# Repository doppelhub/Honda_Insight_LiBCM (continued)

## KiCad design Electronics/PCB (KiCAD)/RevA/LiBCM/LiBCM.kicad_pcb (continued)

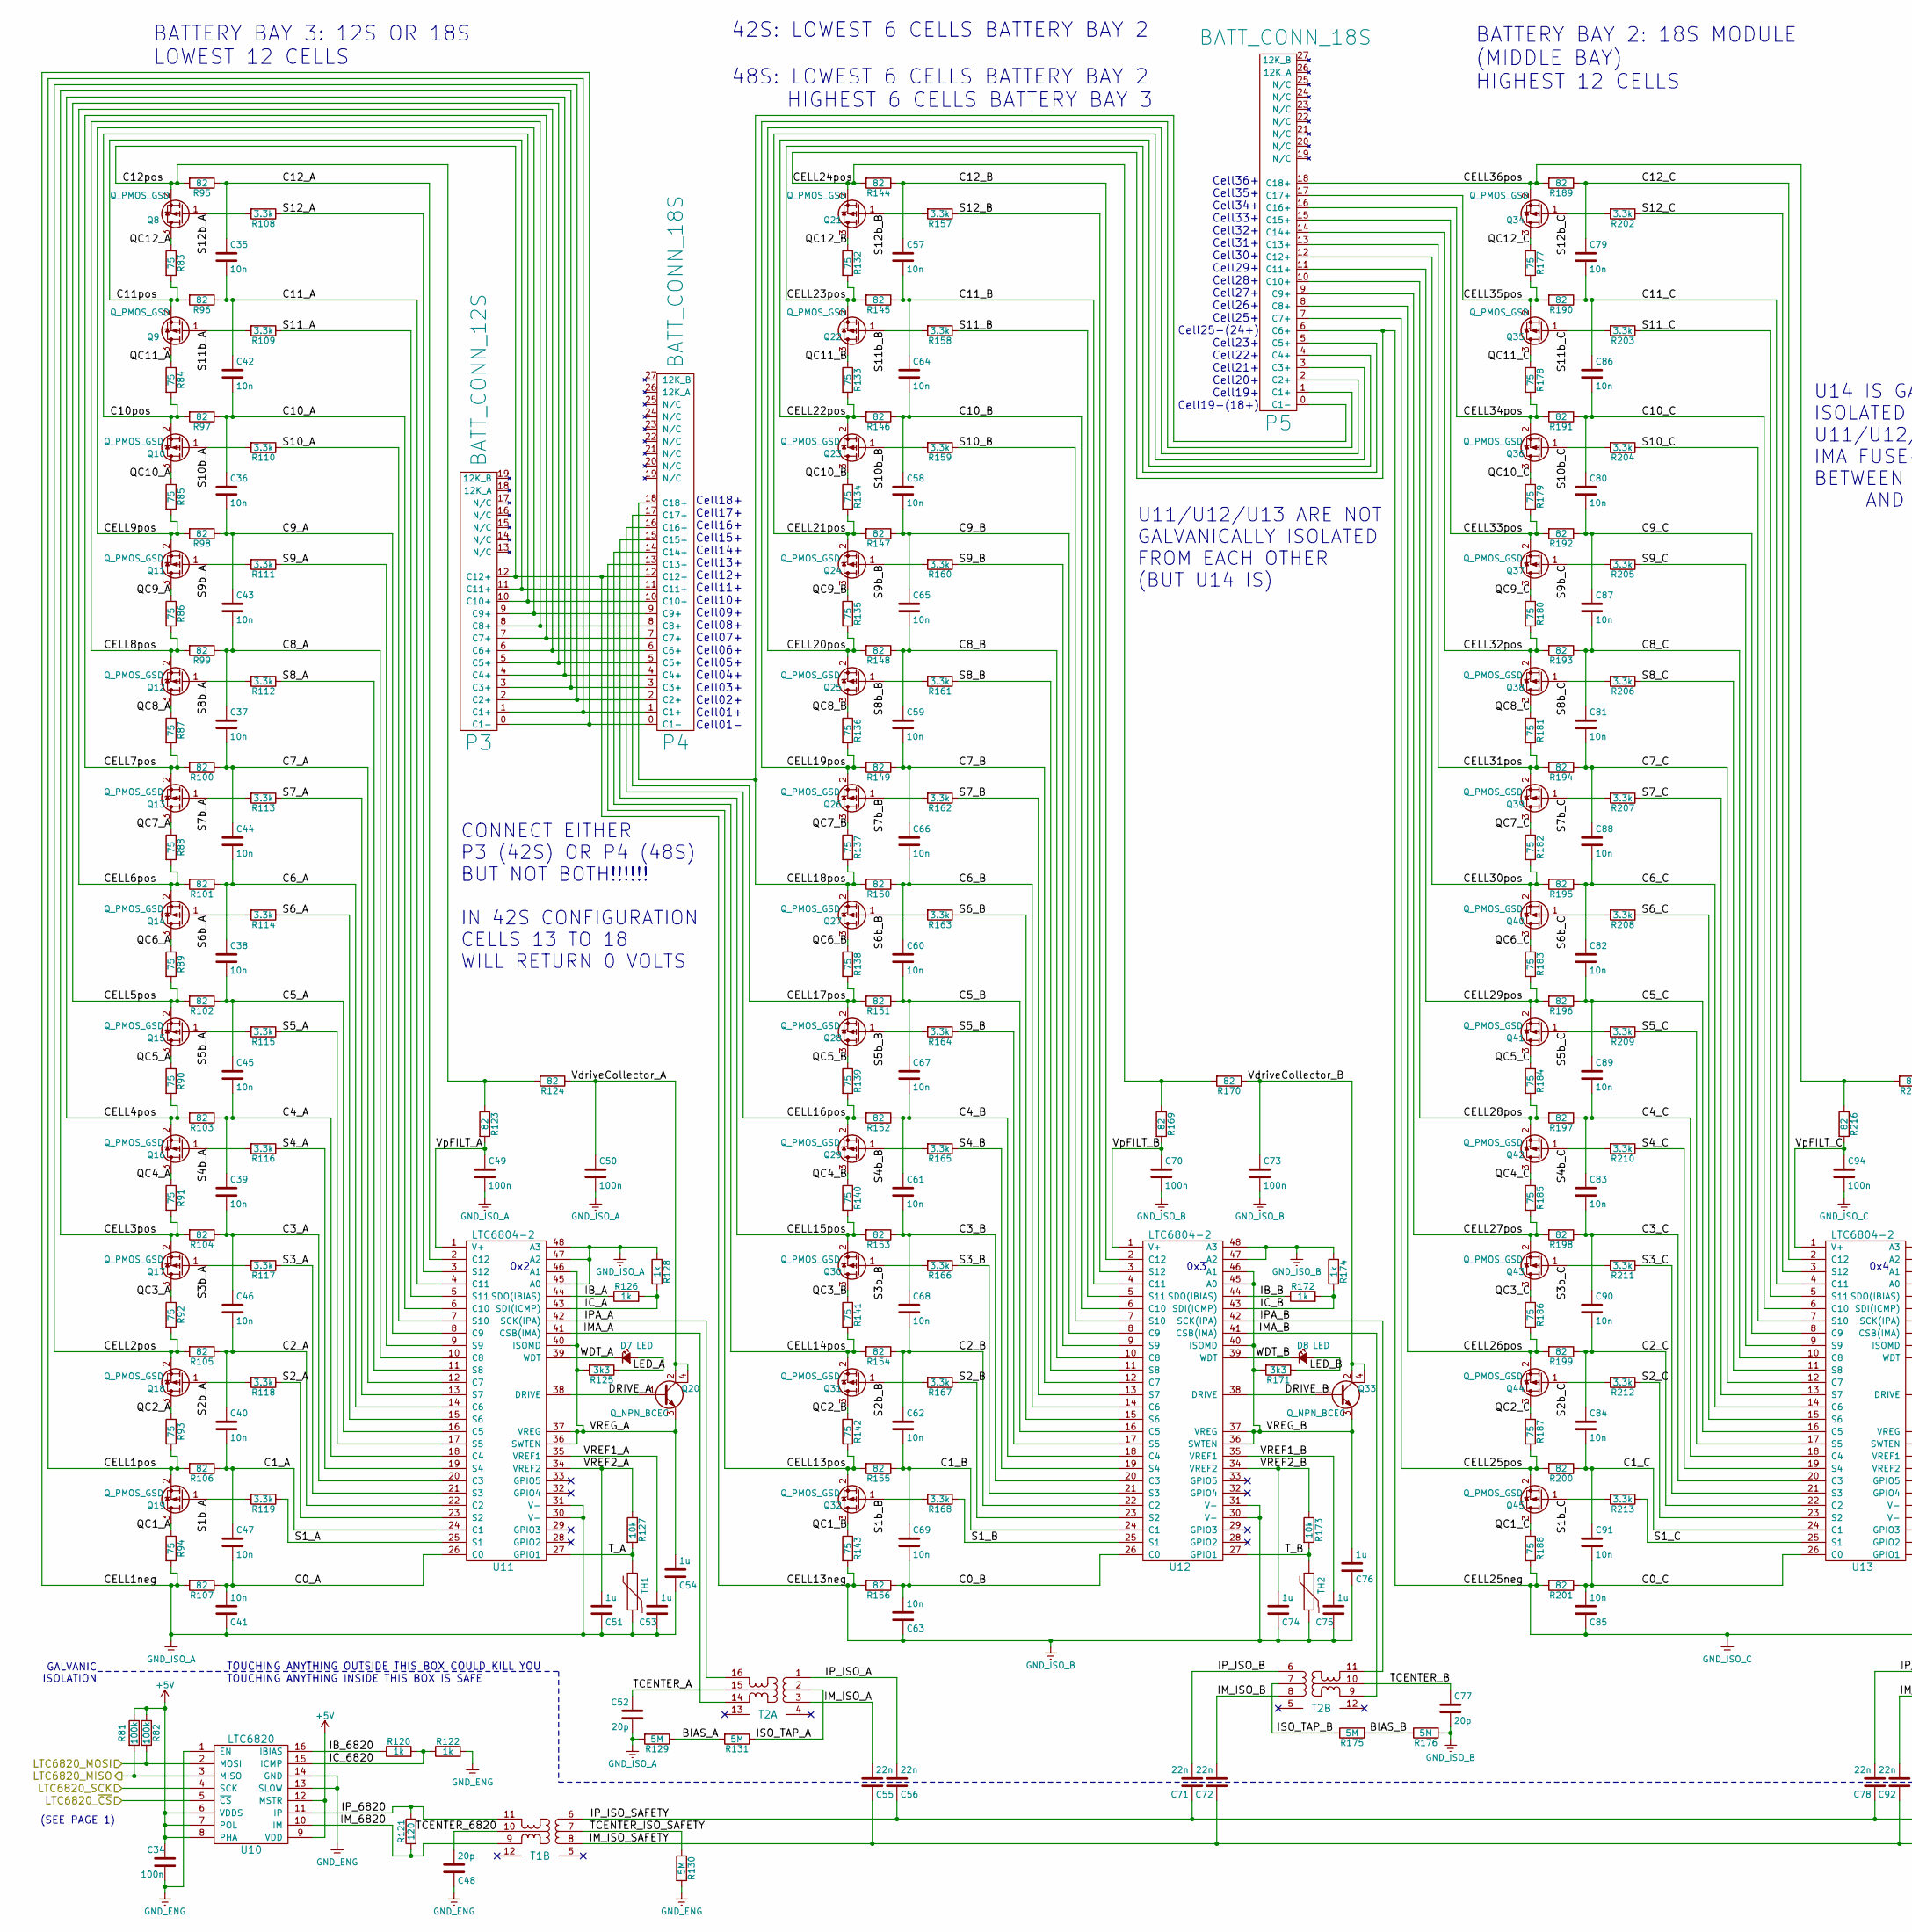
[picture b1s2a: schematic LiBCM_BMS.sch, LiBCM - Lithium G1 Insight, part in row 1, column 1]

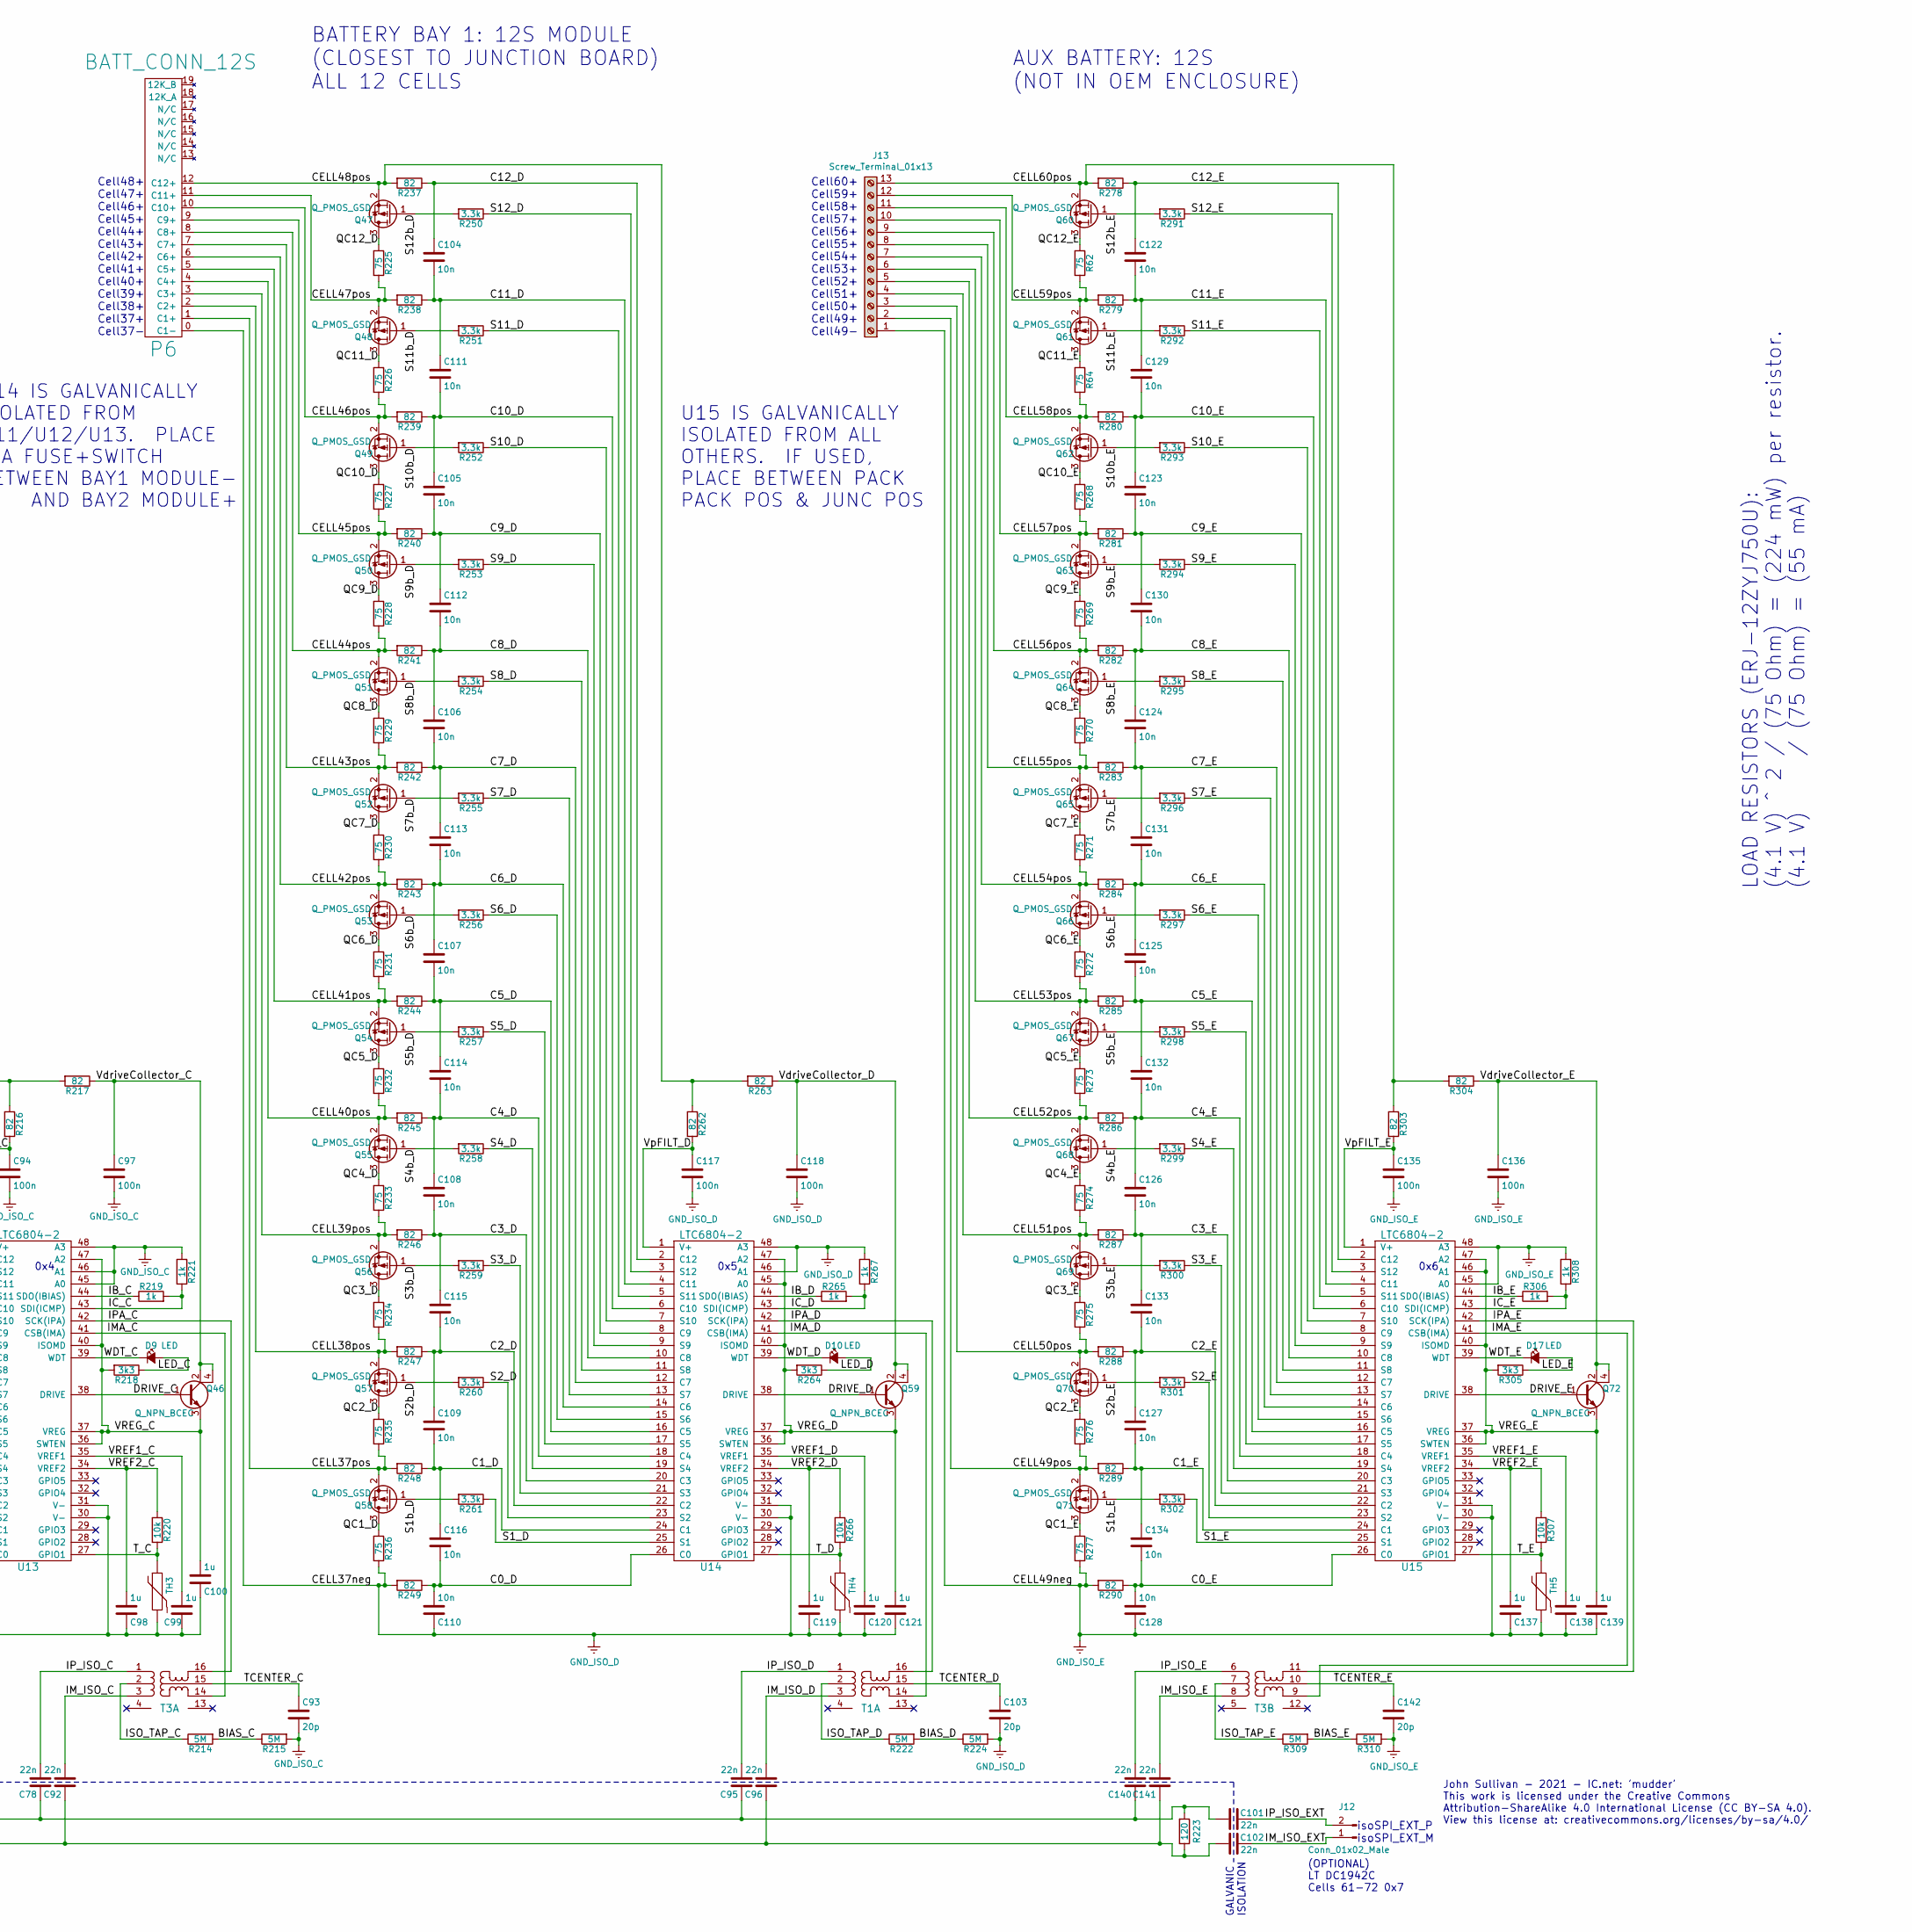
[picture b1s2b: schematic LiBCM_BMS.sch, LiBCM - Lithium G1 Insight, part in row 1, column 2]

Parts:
C34, C49, C50, C70, C73, C94, C97, C117, C118, C135, C136: 100n; C_0805_2012Metric
C35, C36, C37, C38, C39, C40, C41, C42, C43, C44, C45, C46, C47, C57, C58, C59, C60, C61, C62, C63, C64, C65, C66, C67, C68, C69, C79, C80, C81, C82, C83, C84, C85, C86, C87, C88, C89, C90, C91, C104, C105, C106, C107, C108, C109, C110, C111, C112, C113, C114, C115, C116, C122, C123, C124, C125, C126, C127, C128, C129, C130, C131, C132, C133, C134: 10n; C_0805_2012Metric
C48, C52, C77, C93, C103, C142: 20p; C_0805_2012Metric
C51, C53, C54, C74, C75, C76, C98, C99, C100, C119, C120, C121, C137, C138, C139: 1u; C_0805_2012Metric
C55, C56, C71, C72, C78, C92, C95, C96, C101, C102, C140, C141: 22n; C_1206_3216Metric
D7, D8, D9, D10, D17: LED; LED_0805_2012Metric_Castellated
J12: Conn_01x02_Male; SolderWire-0.25sqmm_1x02_P4.2mm_D0.65mm_OD1.7mm
J13: Screw_Terminal_01x13; Conn_277-1232-ND
P3, P6: BATT_CONN_12S; CONN_HONDA-12S
P4, P5: BATT_CONN_18S; CONN_HONDA-18S
Q8, Q9, Q10, Q11, Q12, Q13, Q14, Q15, Q16, Q17, Q18, Q19, Q21, Q22, Q23, Q24, Q25, Q26, Q27, Q28, Q29, Q30, Q31, Q32, Q34, Q35, Q36, Q37, Q38, Q39, Q40, Q41, Q42, Q43, Q44, Q45, Q47, Q48, Q49, Q50, Q51, Q52, Q53, Q54, Q55, Q56, Q57, Q58, Q60, Q61, Q62, Q63, Q64, Q65, Q66, Q67, Q68, Q69, Q70, Q71: Q_PMOS_GSD; SOT-23; Digikey BSS308PE-H6327TR-ND
Q20, Q33, Q46, Q59, Q72: Q_NPN_BCEC; SOT-223; Digikey BCP56-16T1GOSTR-ND
R62, R64, R83, R84, R85, R86, R87, R88, R89, R90, R91, R92, R93, R94, R132, R133, R134, R135, R136, R137, R138, R139, R140, R141, R142, R143, R177, R178, R179, R180, R181, R182, R183, R184, R185, R186, R187, R188, R225, R226, R227, R228, R229, R230, R231, R232, R233, R234, R235, R236, R268, R269, R270, R271, R272, R273, R274, R275, R276, R277: 75; R_2010_5025Metric
R81, R82: 100k; R_0805_2012Metric
R95, R96, R97, R98, R99, R100, R101, R102, R103, R104, R105, R106, R107, R123, R124, R144, R145, R146, R147, R148, R149, R150, R151, R152, R153, R154, R155, R156, R169, R170, R189, R190, R191, R192, R193, R194, R195, R196, R197, R198, R199, R200, R201, R216, R217, R237, R238, R239, R240, R241, R242, R243, R244, R245, R246, R247, R248, R249, R262, R263, R278, R279, R280, R281, R282, R283, R284, R285, R286, R287, R288, R289, R290, R303, R304: 82; R_0805_2012Metric
R108, R109, R110, R111, R112, R113, R114, R115, R116, R117, R118, R119, R157, R158, R159, R160, R161, R162, R163, R164, R165, R166, R167, R168, R202, R203, R204, R205, R206, R207, R208, R209, R210, R211, R212, R213, R250, R251, R252, R253, R254, R255, R256, R257, R258, R259, R260, R261, R291, R292, R293, R294, R295, R296, R297, R298, R299, R300, R301, R302: 3.3k; R_0805_2012Metric
R120, R122, R126, R128, R172, R174, R219, R221, R265, R267, R306, R308: 1k; R_0805_2012Metric
R121, R223: 120; R_0805_2012Metric
R125, R171, R218, R264, R305: 3k3; R_0805_2012Metric
R127, R173, R220, R266, R307: 10k; R_0805_2012Metric
R129, R130, R131, R175, R176, R214, R215, R222, R224, R309, R310: 5M; R_1206_3216Metric
T1, T3: Trans_7490100111; Trans_7490100111A
T2: Trans_7490100111; Trans_7490100111A; Digikey 7490100111A
TH1, TH2, TH3, TH4, TH5: THERMISTOR; R_0805_2012Metric
U10: LTC6820; LTC6820_MSOP
U11, U12, U13, U14, U15: LTC6804-2

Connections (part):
+5V: C34.1, R81.1, R82.1, U10.6 (VDDS), U10.7 (POL), U10.8 (PHA), U10.9 (VDD), U10.12 (MSTR); also elsewhere on the board
/LiBCM BMS/BIAS_A: R129.1, R131.2
/LiBCM BMS/BIAS_B: R175.2, R176.1
/LiBCM BMS/BIAS_C: R214.2, R215.1
/LiBCM BMS/BIAS_D: R222.2, R224.1
/LiBCM BMS/BIAS_E: R309.2, R310.1
/LiBCM BMS/C0_A: C41.2, C47.2, R107.1, U11.26 (C0)
/LiBCM BMS/C0_B: C63.2, C69.2, R156.1, U12.26 (C0)
/LiBCM BMS/C0_C: C85.2, C91.2, R201.1, U13.26 (C0)
/LiBCM BMS/C0_D: C110.2, C116.2, R249.1, U14.26 (C0)
/LiBCM BMS/C0_E: C128.2, C134.2, R290.1, U15.26 (C0)
/LiBCM BMS/C1_A: C40.2, C47.1, R106.1, U11.24 (C1)
/LiBCM BMS/C1_B: C62.2, C69.1, R155.1, U12.24 (C1)
/LiBCM BMS/C1_C: C84.2, C91.1, R200.1, U13.24 (C1)
/LiBCM BMS/C1_D: C109.2, C116.1, R248.1, U14.24 (C1)
/LiBCM BMS/C1_E: C127.2, C134.1, R289.1, U15.24 (C1)
/LiBCM BMS/C2_A: C40.1, C46.2, R105.1, U11.22 (C2)
/LiBCM BMS/C2_B: C62.1, C68.2, R154.1, U12.22 (C2)
/LiBCM BMS/C2_C: C84.1, C90.2, R199.1, U13.22 (C2)
/LiBCM BMS/C2_D: C109.1, C115.2, R247.1, U14.22 (C2)
/LiBCM BMS/C2_E: C127.1, C133.2, R288.1, U15.22 (C2)
/LiBCM BMS/C3_A: C39.2, C46.1, R104.1, U11.20 (C3)
/LiBCM BMS/C3_B: C61.2, C68.1, R153.1, U12.20 (C3)
/LiBCM BMS/C3_C: C83.2, C90.1, R198.1, U13.20 (C3)
/LiBCM BMS/C3_D: C108.2, C115.1, R246.1, U14.20 (C3)
/LiBCM BMS/C3_E: C126.2, C133.1, R287.1, U15.20 (C3)
/LiBCM BMS/C4_A: C39.1, C45.2, R103.1, U11.18 (C4)
/LiBCM BMS/C4_B: C61.1, C67.2, R152.1, U12.18 (C4)
/LiBCM BMS/C4_C: C83.1, C89.2, R197.1, U13.18 (C4)
/LiBCM BMS/C4_D: C108.1, C114.2, R245.1, U14.18 (C4)
/LiBCM BMS/C4_E: C126.1, C132.2, R286.1, U15.18 (C4)
/LiBCM BMS/C5_A: C38.2, C45.1, R102.1, U11.16 (C5)
/LiBCM BMS/C5_B: C60.2, C67.1, R151.1, U12.16 (C5)
/LiBCM BMS/C5_C: C82.2, C89.1, R196.1, U13.16 (C5)
/LiBCM BMS/C5_D: C107.2, C114.1, R244.1, U14.16 (C5)
/LiBCM BMS/C5_E: C125.2, C132.1, R285.1, U15.16 (C5)
/LiBCM BMS/C6_A: C38.1, C44.2, R101.1, U11.14 (C6)
/LiBCM BMS/C6_B: C60.1, C66.2, R150.1, U12.14 (C6)
/LiBCM BMS/C6_C: C82.1, C88.2, R195.1, U13.14 (C6)
/LiBCM BMS/C6_D: C107.1, C113.2, R243.1, U14.14 (C6)
/LiBCM BMS/C6_E: C125.1, C131.2, R284.1, U15.14 (C6)
/LiBCM BMS/C7_A: C37.2, C44.1, R100.1, U11.12 (C7)
/LiBCM BMS/C7_B: C59.2, C66.1, R149.1, U12.12 (C7)
/LiBCM BMS/C7_C: C81.2, C88.1, R194.1, U13.12 (C7)
/LiBCM BMS/C7_D: C106.2, C113.1, R242.1, U14.12 (C7)
/LiBCM BMS/C7_E: C124.2, C131.1, R283.1, U15.12 (C7)
/LiBCM BMS/C8_A: C37.1, C43.2, R99.1, U11.10 (C8)
/LiBCM BMS/C8_B: C59.1, C65.2, R148.1, U12.10 (C8)
/LiBCM BMS/C8_C: C81.1, C87.2, R193.1, U13.10 (C8)
/LiBCM BMS/C8_D: C106.1, C112.2, R241.1, U14.10 (C8)
/LiBCM BMS/C8_E: C124.1, C130.2, R282.1, U15.10 (C8)
/LiBCM BMS/C9_A: C36.2, C43.1, R98.1, U11.8 (C9)
/LiBCM BMS/C9_B: C58.2, C65.1, R147.1, U12.8 (C9)
/LiBCM BMS/C9_C: C80.2, C87.1, R192.1, U13.8 (C9)
/LiBCM BMS/C9_D: C105.2, C112.1, R240.1, U14.8 (C9)
/LiBCM BMS/C9_E: C123.2, C130.1, R281.1, U15.8 (C9)
/LiBCM BMS/C10_A: C36.1, C42.2, R97.1, U11.6 (C10)
/LiBCM BMS/C10_B: C58.1, C64.2, R146.1, U12.6 (C10)
/LiBCM BMS/C10_C: C80.1, C86.2, R191.1, U13.6 (C10)
/LiBCM BMS/C10_D: C105.1, C111.2, R239.1, U14.6 (C10)
/LiBCM BMS/C10_E: C123.1, C129.2, R280.1, U15.6 (C10)
/LiBCM BMS/C10pos: P3.10 (C10+), P4.10 (C10+), Q10.2 (S), R84.2, R97.2
/LiBCM BMS/C11_A: C35.2, C42.1, R96.1, U11.4 (C11)
/LiBCM BMS/C11_B: C57.2, C64.1, R145.1, U12.4 (C11)
/LiBCM BMS/C11_C: C79.2, C86.1, R190.1, U13.4 (C11)
/LiBCM BMS/C11_D: C104.2, C111.1, R238.1, U14.4 (C11)
/LiBCM BMS/C11_E: C122.2, C129.1, R279.1, U15.4 (C11)
/LiBCM BMS/C11pos: P3.11 (C11+), P4.11 (C11+), Q9.2 (S), R83.2, R96.2
/LiBCM BMS/C12_A: C35.1, R95.1, U11.2 (C12)
/LiBCM BMS/C12_B: C57.1, R144.1, U12.2 (C12)
/LiBCM BMS/C12_C: C79.1, R189.1, U13.2 (C12)
/LiBCM BMS/C12_D: C104.1, R237.1, U14.2 (C12)
/LiBCM BMS/C12_E: C122.1, R278.1, U15.2 (C12)
/LiBCM BMS/CELL1pos: P3.1 (C1+), P4.1 (C1+), Q19.2 (S), R93.2, R106.2
/LiBCM BMS/CELL2pos: P3.2 (C2+), P4.2 (C2+), Q18.2 (S), R92.2, R105.2
/LiBCM BMS/CELL3pos: P3.3 (C3+), P4.3 (C3+), Q17.2 (S), R91.2, R104.2
/LiBCM BMS/CELL4pos: P3.4 (C4+), P4.4 (C4+), Q16.2 (S), R90.2, R103.2
/LiBCM BMS/CELL5pos: P3.5 (C5+), P4.5 (C5+), Q15.2 (S), R89.2, R102.2
/LiBCM BMS/CELL6pos: P3.6 (C6+), P4.6 (C6+), Q14.2 (S), R88.2, R101.2
/LiBCM BMS/CELL7pos: P3.7 (C7+), P4.7 (C7+), Q13.2 (S), R87.2, R100.2
/LiBCM BMS/CELL8pos: P3.8 (C8+), P4.8 (C8+), Q12.2 (S), R86.2, R99.2
/LiBCM BMS/CELL9pos: P3.9 (C9+), P4.9 (C9+), Q11.2 (S), R85.2, R98.2
/LiBCM BMS/CELL13pos: P4.13 (C13+), Q32.2 (S), R142.2, R155.2
/LiBCM BMS/CELL14pos: P4.14 (C14+), Q31.2 (S), R141.2, R154.2
/LiBCM BMS/CELL15pos: P4.15 (C15+), Q30.2 (S), R140.2, R153.2
/LiBCM BMS/CELL16pos: P4.16 (C16+), Q29.2 (S), R139.2, R152.2
/LiBCM BMS/CELL17pos: P4.17 (C17+), Q28.2 (S), R138.2, R151.2
/LiBCM BMS/CELL18pos: P4.18 (C18+), P5.0 (C1-), Q27.2 (S), R137.2, R150.2
/LiBCM BMS/CELL19pos: P5.1 (C1+), Q26.2 (S), R136.2, R149.2
/LiBCM BMS/CELL20pos: P5.2 (C2+), Q25.2 (S), R135.2, R148.2
/LiBCM BMS/CELL21pos: P5.3 (C3+), Q24.2 (S), R134.2, R147.2
/LiBCM BMS/CELL22pos: P5.4 (C4+), Q23.2 (S), R133.2, R146.2
/LiBCM BMS/CELL23pos: P5.5 (C5+), Q22.2 (S), R132.2, R145.2
/LiBCM BMS/CELL25pos: P5.7 (C7+), Q45.2 (S), R187.2, R200.2
/LiBCM BMS/CELL26pos: P5.8 (C8+), Q44.2 (S), R186.2, R199.2
/LiBCM BMS/CELL27pos: P5.9 (C9+), Q43.2 (S), R185.2, R198.2
/LiBCM BMS/CELL28pos: P5.10 (C10+), Q42.2 (S), R184.2, R197.2
/LiBCM BMS/CELL29pos: P5.11 (C11+), Q41.2 (S), R183.2, R196.2
/LiBCM BMS/CELL30pos: P5.12 (C12+), Q40.2 (S), R182.2, R195.2
/LiBCM BMS/CELL31pos: P5.13 (C13+), Q39.2 (S), R181.2, R194.2
/LiBCM BMS/CELL32pos: P5.14 (C14+), Q38.2 (S), R180.2, R193.2
/LiBCM BMS/CELL33pos: P5.15 (C15+), Q37.2 (S), R179.2, R192.2
/LiBCM BMS/CELL34pos: P5.16 (C16+), Q36.2 (S), R178.2, R191.2
/LiBCM BMS/CELL35pos: P5.17 (C17+), Q35.2 (S), R177.2, R190.2
/LiBCM BMS/CELL36pos: P5.18 (C18+), Q34.2 (S), R189.2, R216.1, R217.2
/LiBCM BMS/CELL37pos: P6.1 (C1+), Q58.2 (S), R235.2, R248.2
/LiBCM BMS/CELL38pos: P6.2 (C2+), Q57.2 (S), R234.2, R247.2
/LiBCM BMS/CELL39pos: P6.3 (C3+), Q56.2 (S), R233.2, R246.2
/LiBCM BMS/CELL40pos: P6.4 (C4+), Q55.2 (S), R232.2, R245.2
/LiBCM BMS/CELL41pos: P6.5 (C5+), Q54.2 (S), R231.2, R244.2
/LiBCM BMS/CELL42pos: P6.6 (C6+), Q53.2 (S), R230.2, R243.2
/LiBCM BMS/CELL43pos: P6.7 (C7+), Q52.2 (S), R229.2, R242.2
/LiBCM BMS/CELL44pos: P6.8 (C8+), Q51.2 (S), R228.2, R241.2
/LiBCM BMS/CELL45pos: P6.9 (C9+), Q50.2 (S), R227.2, R240.2
/LiBCM BMS/CELL46pos: P6.10 (C10+), Q49.2 (S), R226.2, R239.2
/LiBCM BMS/CELL47pos: P6.11 (C11+), Q48.2 (S), R225.2, R238.2
/LiBCM BMS/CELL48pos: P6.12 (C12+), Q47.2 (S), R237.2, R262.1, R263.2
/LiBCM BMS/CELL49pos: J13.2, Q71.2 (S), R276.2, R289.2
/LiBCM BMS/CELL50pos: J13.3, Q70.2 (S), R275.2, R288.2
/LiBCM BMS/CELL51pos: J13.4, Q69.2 (S), R274.2, R287.2
/LiBCM BMS/CELL52pos: J13.5, Q68.2 (S), R273.2, R286.2
/LiBCM BMS/CELL53pos: J13.6, Q67.2 (S), R272.2, R285.2
/LiBCM BMS/CELL54pos: J13.7, Q66.2 (S), R271.2, R284.2
/LiBCM BMS/CELL55pos: J13.8, Q65.2 (S), R270.2, R283.2
/LiBCM BMS/CELL56pos: J13.9, Q64.2 (S), R269.2, R282.2
/LiBCM BMS/CELL57pos: J13.10, Q63.2 (S), R268.2, R281.2
/LiBCM BMS/CELL58pos: J13.11, Q62.2 (S), R64.2, R280.2
/LiBCM BMS/CELL59pos: J13.12, Q61.2 (S), R62.2, R279.2
/LiBCM BMS/CELL60pos: J13.13, Q60.2 (S), R278.2, R303.1, R304.2
/LiBCM BMS/DRIVE_A: Q20.1 (B), U11.38 (DRIVE)
/LiBCM BMS/DRIVE_B: Q33.1 (B), U12.38 (DRIVE)
/LiBCM BMS/DRIVE_C: Q46.1 (B), U13.38 (DRIVE)
/LiBCM BMS/DRIVE_D: Q59.1 (B), U14.38 (DRIVE)
/LiBCM BMS/DRIVE_E: Q72.1 (B), U15.38 (DRIVE)
/LiBCM BMS/IB_6820: R120.1, U10.16 (IBIAS)
/LiBCM BMS/IB_A: R126.1, U11.44 (SDO(IBIAS))
/LiBCM BMS/IB_B: R172.1, U12.44 (SDO(IBIAS))
/LiBCM BMS/IB_C: R219.1, U13.44 (SDO(IBIAS))
/LiBCM BMS/IB_D: R265.1, U14.44 (SDO(IBIAS))
/LiBCM BMS/IB_E: R306.1, U15.44 (SDO(IBIAS))
/LiBCM BMS/IC_6820: R120.2, R122.1, U10.15 (ICMP)
/LiBCM BMS/IC_A: R126.2, R128.2, U11.43 (SDI(ICMP))
/LiBCM BMS/IC_B: R172.2, R174.2, U12.43 (SDI(ICMP))
/LiBCM BMS/IC_C: R219.2, R221.2, U13.43 (SDI(ICMP))
/LiBCM BMS/IC_D: R265.2, R267.2, U14.43 (SDI(ICMP))
/LiBCM BMS/IC_E: R306.2, R308.2, U15.43 (SDI(ICMP))
/LiBCM BMS/IMA_A: T2.14, U11.41 (CSB(IMA))
/LiBCM BMS/IMA_B: T2.9, U12.41 (CSB(IMA))
/LiBCM BMS/IMA_C: T3.14, U13.41 (CSB(IMA))
/LiBCM BMS/IMA_D: T1.14, U14.41 (CSB(IMA))
/LiBCM BMS/IMA_E: T3.9, U15.41 (CSB(IMA))
/LiBCM BMS/IM_6820: R121.2, T1.9, U10.10 (IM)
/LiBCM BMS/IM_ISO_A: C55.2, T2.3
/LiBCM BMS/IM_ISO_B: C72.2, T2.8
/LiBCM BMS/IM_ISO_C: C92.2, T3.3
/LiBCM BMS/IM_ISO_D: C96.2, T1.3
/LiBCM BMS/IM_ISO_E: C141.2, T3.8
/LiBCM BMS/IM_ISO_EXT: C102.2, J12.1
/LiBCM BMS/IM_ISO_SAFETY: C55.1, C72.1, C92.1, C96.1, C102.1, C141.1, R223.1, T1.8
/LiBCM BMS/IPA_A: T2.16, U11.42 (SCK(IPA))
/LiBCM BMS/IPA_B: T2.11, U12.42 (SCK(IPA))
/LiBCM BMS/IPA_C: T3.16, U13.42 (SCK(IPA))
/LiBCM BMS/IPA_D: T1.16, U14.42 (SCK(IPA))
/LiBCM BMS/IPA_E: T3.11, U15.42 (SCK(IPA))
/LiBCM BMS/IP_6820: R121.1, T1.11, U10.11 (IP)
/LiBCM BMS/IP_ISO_A: C56.2, T2.1
/LiBCM BMS/IP_ISO_B: C71.2, T2.6
/LiBCM BMS/IP_ISO_C: C78.2, T3.1
/LiBCM BMS/IP_ISO_D: C95.2, T1.1
/LiBCM BMS/IP_ISO_E: C140.2, T3.6
/LiBCM BMS/IP_ISO_EXT: C101.2, J12.2
/LiBCM BMS/IP_ISO_SAFETY: C56.1, C71.1, C78.1, C95.1, C101.1, C140.1, R223.2, T1.6
/LiBCM BMS/ISO_TAP_A: R131.1, T2.2
/LiBCM BMS/ISO_TAP_B: R175.1, T2.7
/LiBCM BMS/ISO_TAP_C: R214.1, T3.2
/LiBCM BMS/ISO_TAP_D: R222.1, T1.2
/LiBCM BMS/ISO_TAP_E: R309.1, T3.7
/LiBCM BMS/LED_A: D7.2 (A), R125.1
/LiBCM BMS/LED_B: D8.2 (A), R171.1
/LiBCM BMS/LED_C: D9.2 (A), R218.1
/LiBCM BMS/LED_D: D10.2 (A), R264.1
/LiBCM BMS/LED_E: D17.2 (A), R305.1
/LiBCM BMS/QC1_A: Q19.3 (D), R94.1
/LiBCM BMS/QC1_B: Q32.3 (D), R143.1
/LiBCM BMS/QC1_C: Q45.3 (D), R188.1
/LiBCM BMS/QC1_D: Q58.3 (D), R236.1
/LiBCM BMS/QC1_E: Q71.3 (D), R277.1
/LiBCM BMS/QC2_A: Q18.3 (D), R93.1
/LiBCM BMS/QC2_B: Q31.3 (D), R142.1
/LiBCM BMS/QC2_C: Q44.3 (D), R187.1
/LiBCM BMS/QC2_D: Q57.3 (D), R235.1
/LiBCM BMS/QC2_E: Q70.3 (D), R276.1
/LiBCM BMS/QC3_A: Q17.3 (D), R92.1
/LiBCM BMS/QC3_B: Q30.3 (D), R141.1
/LiBCM BMS/QC3_C: Q43.3 (D), R186.1
/LiBCM BMS/QC3_D: Q56.3 (D), R234.1
/LiBCM BMS/QC3_E: Q69.3 (D), R275.1
/LiBCM BMS/QC4_A: Q16.3 (D), R91.1
/LiBCM BMS/QC4_B: Q29.3 (D), R140.1
/LiBCM BMS/QC4_C: Q42.3 (D), R185.1
/LiBCM BMS/QC4_D: Q55.3 (D), R233.1
/LiBCM BMS/QC4_E: Q68.3 (D), R274.1
/LiBCM BMS/QC5_A: Q15.3 (D), R90.1
/LiBCM BMS/QC5_B: Q28.3 (D), R139.1
/LiBCM BMS/QC5_C: Q41.3 (D), R184.1
/LiBCM BMS/QC5_D: Q54.3 (D), R232.1
/LiBCM BMS/QC5_E: Q67.3 (D), R273.1
/LiBCM BMS/QC6_A: Q14.3 (D), R89.1
/LiBCM BMS/QC6_B: Q27.3 (D), R138.1
/LiBCM BMS/QC6_C: Q40.3 (D), R183.1
/LiBCM BMS/QC6_D: Q53.3 (D), R231.1
/LiBCM BMS/QC6_E: Q66.3 (D), R272.1
/LiBCM BMS/QC7_A: Q13.3 (D), R88.1
/LiBCM BMS/QC7_B: Q26.3 (D), R137.1
/LiBCM BMS/QC7_C: Q39.3 (D), R182.1
/LiBCM BMS/QC7_D: Q52.3 (D), R230.1
/LiBCM BMS/QC7_E: Q65.3 (D), R271.1
/LiBCM BMS/QC8_A: Q12.3 (D), R87.1
/LiBCM BMS/QC8_B: Q25.3 (D), R136.1
/LiBCM BMS/QC8_C: Q38.3 (D), R181.1
/LiBCM BMS/QC8_D: Q51.3 (D), R229.1
/LiBCM BMS/QC8_E: Q64.3 (D), R270.1
/LiBCM BMS/QC9_A: Q11.3 (D), R86.1
/LiBCM BMS/QC9_B: Q24.3 (D), R135.1
/LiBCM BMS/QC9_C: Q37.3 (D), R180.1
/LiBCM BMS/QC9_D: Q50.3 (D), R228.1
/LiBCM BMS/QC9_E: Q63.3 (D), R269.1
/LiBCM BMS/QC10_A: Q10.3 (D), R85.1
/LiBCM BMS/QC10_B: Q23.3 (D), R134.1
/LiBCM BMS/QC10_C: Q36.3 (D), R179.1
/LiBCM BMS/QC10_D: Q49.3 (D), R227.1
/LiBCM BMS/QC10_E: Q62.3 (D), R268.1
/LiBCM BMS/QC11_A: Q9.3 (D), R84.1
/LiBCM BMS/QC11_B: Q22.3 (D), R133.1
/LiBCM BMS/QC11_C: Q35.3 (D), R178.1
/LiBCM BMS/QC11_D: Q48.3 (D), R226.1
/LiBCM BMS/QC11_E: Q61.3 (D), R64.1
/LiBCM BMS/QC12_A: Q8.3 (D), R83.1
/LiBCM BMS/QC12_B: Q21.3 (D), R132.1
/LiBCM BMS/QC12_C: Q34.3 (D), R177.1
/LiBCM BMS/QC12_D: Q47.3 (D), R225.1
/LiBCM BMS/QC12_E: Q60.3 (D), R62.1
/LiBCM BMS/S1_A: R119.1, U11.25 (S1)
/LiBCM BMS/S1_B: R168.1, U12.25 (S1)
/LiBCM BMS/S1_C: R213.1, U13.25 (S1)
/LiBCM BMS/S1_D: R261.1, U14.25 (S1)
/LiBCM BMS/S1_E: R302.1, U15.25 (S1)
/LiBCM BMS/S1b_A: Q19.1 (G), R119.2
/LiBCM BMS/S1b_B: Q32.1 (G), R168.2
/LiBCM BMS/S1b_C: Q45.1 (G), R213.2
/LiBCM BMS/S1b_D: Q58.1 (G), R261.2
/LiBCM BMS/S1b_E: Q71.1 (G), R302.2
/LiBCM BMS/S2_A: R118.1, U11.23 (S2)
/LiBCM BMS/S2_B: R167.1, U12.23 (S2)
/LiBCM BMS/S2_C: R212.1, U13.23 (S2)
/LiBCM BMS/S2_D: R260.1, U14.23 (S2)
/LiBCM BMS/S2_E: R301.1, U15.23 (S2)
/LiBCM BMS/S2b_A: Q18.1 (G), R118.2
/LiBCM BMS/S2b_B: Q31.1 (G), R167.2
/LiBCM BMS/S2b_C: Q44.1 (G), R212.2
/LiBCM BMS/S2b_D: Q57.1 (G), R260.2
/LiBCM BMS/S2b_E: Q70.1 (G), R301.2
/LiBCM BMS/S3_A: R117.1, U11.21 (S3)
/LiBCM BMS/S3_B: R166.1, U12.21 (S3)
/LiBCM BMS/S3_C: R211.1, U13.21 (S3)
/LiBCM BMS/S3_D: R259.1, U14.21 (S3)
/LiBCM BMS/S3_E: R300.1, U15.21 (S3)
/LiBCM BMS/S3b_A: Q17.1 (G), R117.2
/LiBCM BMS/S3b_B: Q30.1 (G), R166.2
/LiBCM BMS/S3b_C: Q43.1 (G), R211.2
/LiBCM BMS/S3b_D: Q56.1 (G), R259.2
/LiBCM BMS/S3b_E: Q69.1 (G), R300.2
/LiBCM BMS/S4_A: R116.1, U11.19 (S4)
/LiBCM BMS/S4_B: R165.1, U12.19 (S4)
/LiBCM BMS/S4_C: R210.1, U13.19 (S4)
/LiBCM BMS/S4_D: R258.1, U14.19 (S4)
/LiBCM BMS/S4_E: R299.1, U15.19 (S4)
/LiBCM BMS/S4b_A: Q16.1 (G), R116.2
/LiBCM BMS/S4b_B: Q29.1 (G), R165.2
/LiBCM BMS/S4b_C: Q42.1 (G), R210.2
/LiBCM BMS/S4b_D: Q55.1 (G), R258.2
/LiBCM BMS/S4b_E: Q68.1 (G), R299.2
/LiBCM BMS/S5_A: R115.1, U11.17 (S5)
/LiBCM BMS/S5_B: R164.1, U12.17 (S5)
/LiBCM BMS/S5_C: R209.1, U13.17 (S5)
/LiBCM BMS/S5_D: R257.1, U14.17 (S5)
/LiBCM BMS/S5_E: R298.1, U15.17 (S5)
/LiBCM BMS/S5b_A: Q15.1 (G), R115.2
/LiBCM BMS/S5b_B: Q28.1 (G), R164.2
/LiBCM BMS/S5b_C: Q41.1 (G), R209.2
/LiBCM BMS/S5b_D: Q54.1 (G), R257.2
/LiBCM BMS/S5b_E: Q67.1 (G), R298.2
/LiBCM BMS/S6_A: R114.1, U11.15 (S6)
/LiBCM BMS/S6_B: R163.1, U12.15 (S6)
/LiBCM BMS/S6_C: R208.1, U13.15 (S6)
/LiBCM BMS/S6_D: R256.1, U14.15 (S6)
/LiBCM BMS/S6_E: R297.1, U15.15 (S6)
/LiBCM BMS/S6b_A: Q14.1 (G), R114.2
/LiBCM BMS/S6b_B: Q27.1 (G), R163.2
/LiBCM BMS/S6b_C: Q40.1 (G), R208.2
/LiBCM BMS/S6b_D: Q53.1 (G), R256.2
/LiBCM BMS/S6b_E: Q66.1 (G), R297.2
/LiBCM BMS/S7_A: R113.1, U11.13 (S7)
/LiBCM BMS/S7_B: R162.1, U12.13 (S7)
/LiBCM BMS/S7_C: R207.1, U13.13 (S7)
/LiBCM BMS/S7_D: R255.1, U14.13 (S7)
/LiBCM BMS/S7_E: R296.1, U15.13 (S7)
/LiBCM BMS/S7b_A: Q13.1 (G), R113.2
/LiBCM BMS/S7b_B: Q26.1 (G), R162.2
/LiBCM BMS/S7b_C: Q39.1 (G), R207.2
/LiBCM BMS/S7b_D: Q52.1 (G), R255.2
/LiBCM BMS/S7b_E: Q65.1 (G), R296.2
/LiBCM BMS/S8_A: R112.1, U11.11 (S8)
/LiBCM BMS/S8_B: R161.1, U12.11 (S8)
/LiBCM BMS/S8_C: R206.1, U13.11 (S8)
/LiBCM BMS/S8_D: R254.1, U14.11 (S8)
/LiBCM BMS/S8_E: R295.1, U15.11 (S8)
/LiBCM BMS/S8b_A: Q12.1 (G), R112.2
/LiBCM BMS/S8b_B: Q25.1 (G), R161.2
/LiBCM BMS/S8b_C: Q38.1 (G), R206.2
/LiBCM BMS/S8b_D: Q51.1 (G), R254.2
/LiBCM BMS/S8b_E: Q64.1 (G), R295.2
/LiBCM BMS/S9_A: R111.1, U11.9 (S9)
/LiBCM BMS/S9_B: R160.1, U12.9 (S9)
/LiBCM BMS/S9_C: R205.1, U13.9 (S9)
/LiBCM BMS/S9_D: R253.1, U14.9 (S9)
/LiBCM BMS/S9_E: R294.1, U15.9 (S9)
/LiBCM BMS/S9b_A: Q11.1 (G), R111.2
/LiBCM BMS/S9b_B: Q24.1 (G), R160.2
/LiBCM BMS/S9b_C: Q37.1 (G), R205.2
/LiBCM BMS/S9b_D: Q50.1 (G), R253.2
/LiBCM BMS/S9b_E: Q63.1 (G), R294.2
/LiBCM BMS/S10_A: R110.1, U11.7 (S10)
/LiBCM BMS/S10_B: R159.1, U12.7 (S10)
/LiBCM BMS/S10_C: R204.1, U13.7 (S10)
/LiBCM BMS/S10_D: R252.1, U14.7 (S10)
/LiBCM BMS/S10_E: R293.1, U15.7 (S10)
/LiBCM BMS/S10b_A: Q10.1 (G), R110.2
/LiBCM BMS/S10b_B: Q23.1 (G), R159.2
/LiBCM BMS/S10b_C: Q36.1 (G), R204.2
/LiBCM BMS/S10b_D: Q49.1 (G), R252.2
/LiBCM BMS/S10b_E: Q62.1 (G), R293.2
/LiBCM BMS/S11_A: R109.1, U11.5 (S11)
/LiBCM BMS/S11_B: R158.1, U12.5 (S11)
/LiBCM BMS/S11_C: R203.1, U13.5 (S11)
/LiBCM BMS/S11_D: R251.1, U14.5 (S11)
/LiBCM BMS/S11_E: R292.1, U15.5 (S11)
/LiBCM BMS/S11b_A: Q9.1 (G), R109.2
/LiBCM BMS/S11b_B: Q22.1 (G), R158.2
/LiBCM BMS/S11b_C: Q35.1 (G), R203.2
/LiBCM BMS/S11b_D: Q48.1 (G), R251.2
/LiBCM BMS/S11b_E: Q61.1 (G), R292.2
/LiBCM BMS/S12_A: R108.1, U11.3 (S12)
/LiBCM BMS/S12_B: R157.1, U12.3 (S12)
/LiBCM BMS/S12_C: R202.1, U13.3 (S12)
/LiBCM BMS/S12_D: R250.1, U14.3 (S12)
/LiBCM BMS/S12_E: R291.1, U15.3 (S12)
/LiBCM BMS/S12b_A: Q8.1 (G), R108.2
/LiBCM BMS/S12b_B: Q21.1 (G), R157.2
/LiBCM BMS/S12b_C: Q34.1 (G), R202.2
/LiBCM BMS/S12b_D: Q47.1 (G), R250.2
/LiBCM BMS/S12b_E: Q60.1 (G), R291.2
/LiBCM BMS/TCENTER_6820: C48.2, T1.10
/LiBCM BMS/TCENTER_A: C52.1, T2.15
/LiBCM BMS/TCENTER_B: C77.1, T2.10
/LiBCM BMS/TCENTER_C: C93.1, T3.15
/LiBCM BMS/TCENTER_D: C103.1, T1.15
/LiBCM BMS/TCENTER_E: C142.1, T3.10
/LiBCM BMS/TCENTER_ISO_SAFETY: R130.1, T1.7
/LiBCM BMS/T_A: R127.2, TH1.1, U11.27 (GPIO1)
/LiBCM BMS/T_B: R173.2, TH2.1, U12.27 (GPIO1)
/LiBCM BMS/T_C: R220.2, TH3.1, U13.27 (GPIO1)
/LiBCM BMS/T_D: R266.2, TH4.1, U14.27 (GPIO1)
/LiBCM BMS/T_E: R307.2, TH5.1, U15.27 (GPIO1)
/LiBCM BMS/VREF1_A: C53.2, U11.35 (VREF1)
/LiBCM BMS/VREF1_B: C75.2, U12.35 (VREF1)
/LiBCM BMS/VREF1_C: C99.2, U13.35 (VREF1)
/LiBCM BMS/VREF1_D: C120.2, U14.35 (VREF1)
/LiBCM BMS/VREF1_E: C138.2, U15.35 (VREF1)
/LiBCM BMS/VREF2_A: C51.2, R127.1, U11.34 (VREF2)
/LiBCM BMS/VREF2_B: C74.2, R173.1, U12.34 (VREF2)
/LiBCM BMS/VREF2_C: C98.2, R220.1, U13.34 (VREF2)
/LiBCM BMS/VREF2_D: C119.2, R266.1, U14.34 (VREF2)
/LiBCM BMS/VREF2_E: C137.2, R307.1, U15.34 (VREF2)
/LiBCM BMS/VREG_A: C54.2, Q20.3 (E), R125.2, U11.36 (SWTEN), U11.37 (VREG), U11.40 (ISOMD), U11.46 (A1)
/LiBCM BMS/VREG_B: C76.2, Q33.3 (E), R171.2, U12.36 (SWTEN), U12.37 (VREG), U12.40 (ISOMD), U12.45 (A0), U12.46 (A1)
/LiBCM BMS/VREG_C: C100.2, Q46.3 (E), R218.2, U13.36 (SWTEN), U13.37 (VREG), U13.40 (ISOMD), U13.47 (A2)
/LiBCM BMS/VREG_D: C121.2, Q59.3 (E), R264.2, U14.36 (SWTEN), U14.37 (VREG), U14.40 (ISOMD), U14.45 (A0), U14.47 (A2)
/LiBCM BMS/VREG_E: C139.2, Q72.3 (E), R305.2, U15.36 (SWTEN), U15.37 (VREG), U15.40 (ISOMD), U15.46 (A1), U15.47 (A2)
/LiBCM BMS/VdriveCollector_A: C50.1, Q20.2 (C), Q20.4 (C), R124.1
/LiBCM BMS/VdriveCollector_B: C73.1, Q33.2 (C), Q33.4 (C), R170.1
/LiBCM BMS/VdriveCollector_C: C97.1, Q46.2 (C), Q46.4 (C), R217.1
/LiBCM BMS/VdriveCollector_D: C118.1, Q59.2 (C), Q59.4 (C), R263.1
/LiBCM BMS/VdriveCollector_E: C136.1, Q72.2 (C), Q72.4 (C), R304.1
/LiBCM BMS/VpFILT_A: C49.1, R123.2, U11.1 (V+)
/LiBCM BMS/VpFILT_B: C70.1, R169.2, U12.1 (V+)
/LiBCM BMS/VpFILT_C: C94.1, R216.2, U13.1 (V+)
/LiBCM BMS/VpFILT_D: C117.1, R262.2, U14.1 (V+)
/LiBCM BMS/VpFILT_E: C135.1, R303.2, U15.1 (V+)
/LiBCM BMS/WDT_A: D7.1 (K), U11.39 (WDT)
/LiBCM BMS/WDT_B: D8.1 (K), U12.39 (WDT)
/LiBCM BMS/WDT_C: D9.1 (K), U13.39 (WDT)
/LiBCM BMS/WDT_D: D10.1 (K), U14.39 (WDT)
/LiBCM BMS/WDT_E: D17.1 (K), U15.39 (WDT)
/SPI_BATT_CS0: U10.5 (~CS); also elsewhere on the board
/SPI_BATT_MISO: R81.2, U10.3 (MISO); also elsewhere on the board
/SPI_BATT_MOSI: R82.2, U10.2 (MOSI); also elsewhere on the board
/SPI_BATT_SCK: U10.4 (SCK); also elsewhere on the board
GND_ENG: C34.2, C48.1, R122.2, R130.2, U10.1 (EN), U10.13 (SLOW), U10.14 (GND); also elsewhere on the board
GND_ISO_A: C41.1, C49.2, C50.2, C51.1, C52.2, C53.1, C54.1, P3.0 (C1-), P4.0 (C1-), R94.2, R107.2, R128.1, R129.2, TH1.2, U11.30 (V-), U11.31 (V-), U11.45 (A0), U11.47 (A2), U11.48 (A3)
GND_ISO_B: C63.1, C70.2, C73.2, C74.1, C75.1, C76.1, C77.2, P3.12 (C12+), P4.12 (C12+), Q8.2 (S), R95.2, R123.1, R124.2, R143.2, R156.2, R174.1, R176.2, TH2.2, U12.30 (V-), U12.31 (V-), U12.47 (A2), U12.48 (A3)
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
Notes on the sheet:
0x2
0x3
Cell18+ Cell17+ Cell16+ Cell15+ Cell14+ Cell13+ Cell12+ Cell11+ Cell10+ Cell09+ Cell08+ Cell07+ Cell06+ Cell05+ Cell04+ Cell03+ Cell02+ Cell01+ Cell01-
(OPTIONAL) LT DC1942C Cells 61-72 0x7
0x5
Cell48+ Cell47+ Cell46+ Cell45+ Cell44+ Cell43+ Cell42+ Cell41+ Cell40+ Cell39+ Cell38+ Cell37+ Cell37-
Cell36+ Cell35+ Cell34+ Cell33+ Cell32+ Cell31+ Cell30+ Cell29+ Cell28+ Cell27+ Cell26+ Cell25+ Cell25-(24+) Cell23+ Cell22+ Cell21+ Cell20+ Cell19+ Cell19-(18+)
0x4
John Sullivan - 2021 - IC.net: 'mudder' This work is licensed under the Creative Commons Attribution-ShareAlike 4.0 International License (CC BY-SA 4.0). View this license at: creativecommons.org/licenses/by-sa/4.0/
LOAD RESISTORS (ERJ-12ZYJ750U): (4.1 V) ^ 2 / (75 Ohm) = (224 mW) per resistor. (4.1 V) / (75 Ohm) = (55 mA)
TOUCHING ANYTHING INSIDE THIS BOX IS SAFE
TOUCHING ANYTHING OUTSIDE THIS BOX COULD KILL YOU
GALVANIC ISOLATION
BATTERY BAY 1: 12S MODULE (CLOSEST TO JUNCTION BOARD) ALL 12 CELLS
BATTERY BAY 2: 18S MODULE (MIDDLE BAY) HIGHEST 12 CELLS
42S: LOWEST 6 CELLS BATTERY BAY 2 48S: LOWEST 6 CELLS BATTERY BAY 2 HIGHEST 6 CELLS BATTERY BAY 3
BATTERY BAY 3: 12S OR 18S LOWEST 12 CELLS
CONNECT EITHER P3 (42S) OR P4 (48S) BUT NOT BOTH!!!!!! IN 42S CONFIGURATION CELLS 13 TO 18 WILL RETURN 0 VOLTS
U11/U12/U13 ARE NOT GALVANICALLY ISOLATED FROM EACH OTHER (BUT U14 IS)
U14 IS GALVANICALLY ISOLATED FROM U11/U12/U13. PLACE IMA FUSE+SWITCH BETWEEN BAY1 MODULE- AND BAY2 MODULE+
(SEE PAGE 1)
0x6
Cell60+ Cell59+ Cell58+ Cell57+ Cell56+ Cell55+ Cell54+ Cell53+ Cell52+ Cell51+ Cell50+ Cell49+ Cell49-
AUX BATTERY: 12S (NOT IN OEM ENCLOSURE)
U15 IS GALVANICALLY ISOLATED FROM ALL OTHERS. IF USED, PLACE BETWEEN PACK PACK POS & JUNC POS
isoSPI_EXT_P isoSPI_EXT_M
